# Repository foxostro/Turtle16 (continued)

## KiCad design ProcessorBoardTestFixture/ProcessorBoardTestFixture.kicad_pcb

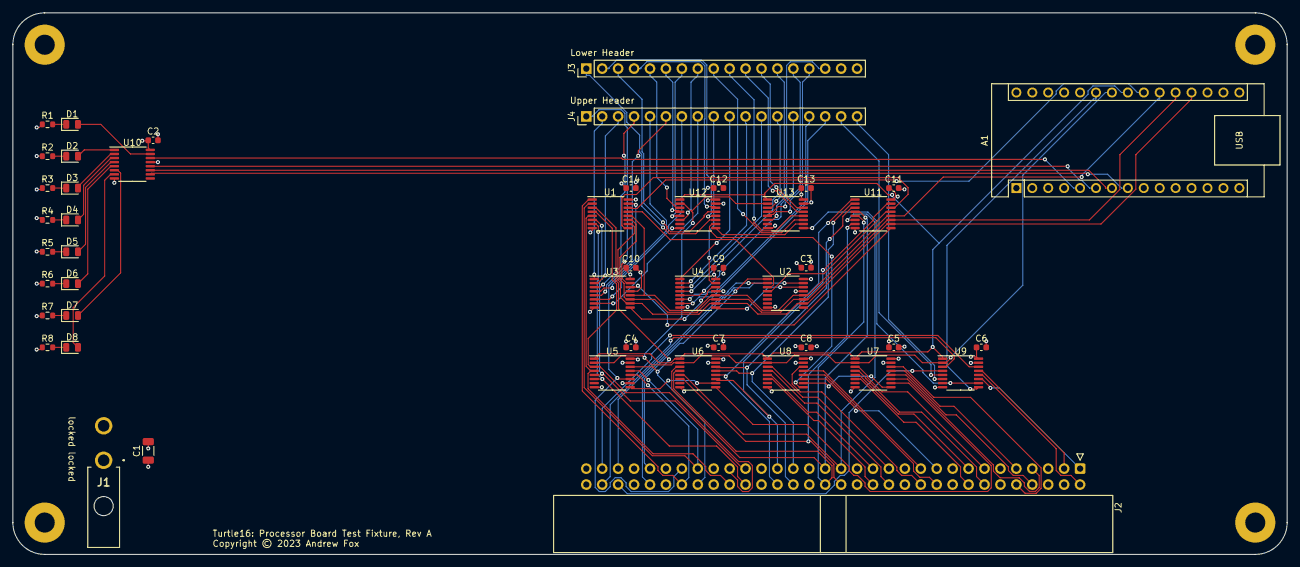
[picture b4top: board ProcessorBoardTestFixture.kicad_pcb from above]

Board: 4 copper layers, 203.2 x 86.4 mm, 52 parts (0 on the bottom side), 116 nets.

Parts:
A1: Arduino_Nano_Every; Arduino_Nano
C1: 100uF; C_1206_3216Metric
C2, C3, C4, C5, C6, C7, C8, C9, C10, C11, C12, C13, C14: 0.1uF; C_0603_1608Metric
D1, D2, D3, D4, D5, D6, D7, D8: Red; LED_0805_2012Metric
H1, H2, H3, H4: MountingHole_Pad; MountingHole_3.2mm_M3_Pad
J1: Power In; 172448-0002
J2: 71922-164LF; IDC-Header_2x32_P2.54mm_Horizontal
J3: Lower Header; PinHeader_1x18_P2.54mm_Vertical
J4: Upper Header; PinHeader_1x18_P2.54mm_Vertical
R1, R2, R3, R4, R5, R6, R7, R8: 270R; R_0603_1608Metric
U1, U2, U3, U4, U10, U11: 74HC595; TSSOP-16_4.4x5mm_P0.65mm
U5, U6, U7, U8, U9, U12, U13: 74HC165; TSSOP-16_4.4x5mm_P0.65mm

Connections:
/Instruction ROM Interface/FLUSH_IF: J4.17, U9.5 (D6)
/Instruction ROM Interface/Ins_IF0: J4.1, U3.15 (QA)
/Instruction ROM Interface/Ins_IF1: J4.2, U3.1 (QB)
/Instruction ROM Interface/Ins_IF2: J4.3, U3.2 (QC)
/Instruction ROM Interface/Ins_IF3: J4.4, U3.3 (QD)
/Instruction ROM Interface/Ins_IF4: J4.5, U3.4 (QE)
/Instruction ROM Interface/Ins_IF5: J4.6, U3.5 (QF)
/Instruction ROM Interface/Ins_IF6: J4.7, U3.6 (QG)
/Instruction ROM Interface/Ins_IF7: J4.8, U3.7 (QH)
/Instruction ROM Interface/Ins_IF8: J4.9, U4.15 (QA)
/Instruction ROM Interface/Ins_IF9: J4.10, U4.1 (QB)
/Instruction ROM Interface/Ins_IF10: J4.11, U4.2 (QC)
/Instruction ROM Interface/Ins_IF11: J4.12, U4.3 (QD)
/Instruction ROM Interface/Ins_IF12: J4.13, U4.4 (QE)
/Instruction ROM Interface/Ins_IF13: J4.14, U4.5 (QF)
/Instruction ROM Interface/Ins_IF14: J4.15, U4.6 (QG)
/Instruction ROM Interface/Ins_IF15: J4.16, U4.7 (QH)
/Instruction ROM Interface/PC0: J3.1, U12.11 (D0)
/Instruction ROM Interface/PC1: J3.2, U12.12 (D1)
/Instruction ROM Interface/PC2: J3.3, U12.13 (D2)
/Instruction ROM Interface/PC3: J3.4, U12.14 (D3)
/Instruction ROM Interface/PC4: J3.5, U12.3 (D4)
/Instruction ROM Interface/PC5: J3.6, U12.4 (D5)
/Instruction ROM Interface/PC6: J3.7, U12.5 (D6)
/Instruction ROM Interface/PC7: J3.8, U12.6 (D7)
/Instruction ROM Interface/PC8: J3.9, U13.11 (D0)
/Instruction ROM Interface/PC9: J3.10, U13.12 (D1)
/Instruction ROM Interface/PC10: J3.11, U13.13 (D2)
/Instruction ROM Interface/PC11: J3.12, U13.14 (D3)
/Instruction ROM Interface/PC12: J3.13, U13.3 (D4)
/Instruction ROM Interface/PC13: J3.14, U13.4 (D5)
/Instruction ROM Interface/PC14: J3.15, U13.5 (D6)
/Instruction ROM Interface/PC15: J3.16, U13.6 (D7)
/Instruction ROM Interface/RAMEN_R: J4.18, U9.6 (D7)
/LED Output/RCLK: A1.6 (D3), U10.12 (RCLK)
/LED Output/SCK: A1.7 (D4), U10.11 (SRCLK)
/LED Output/SI: A1.5 (D2), U10.14 (SER)
/LED Output/~CLR: A1.8 (D5), U10.10 (~SRCLR)
/System Bus Connector/Addr0: J2.7, U7.11 (D0)
/System Bus Connector/Addr1: J2.8, U7.12 (D1)
/System Bus Connector/Addr2: J2.9, U7.13 (D2)
/System Bus Connector/Addr3: J2.10, U7.14 (D3)
/System Bus Connector/Addr4: J2.13, U7.3 (D4)
/System Bus Connector/Addr5: J2.14, U7.4 (D5)
/System Bus Connector/Addr6: J2.15, U7.5 (D6)
/System Bus Connector/Addr7: J2.16, U7.6 (D7)
/System Bus Connector/Addr8: J2.19, U8.11 (D0)
/System Bus Connector/Addr9: J2.20, U8.12 (D1)
/System Bus Connector/Addr10: J2.21, U8.13 (D2)
/System Bus Connector/Addr11: J2.22, U8.14 (D3)
/System Bus Connector/Addr12: J2.25, U8.3 (D4)
/System Bus Connector/Addr13: J2.26, U8.4 (D5)
/System Bus Connector/Addr14: J2.27, U8.5 (D6)
/System Bus Connector/Addr15: J2.28, U8.6 (D7)
/System Bus Connector/Bank0: J2.1, U9.11 (D0)
/System Bus Connector/Bank1: J2.2, U9.12 (D1)
/System Bus Connector/Bank2: J2.3, U9.13 (D2)
/System Bus Connector/IO0: J2.51, U1.15 (QA), U5.11 (D0)
/System Bus Connector/IO1: J2.52, U1.1 (QB), U5.12 (D1)
/System Bus Connector/IO2: J2.49, U1.2 (QC), U5.13 (D2)
/System Bus Connector/IO3: J2.50, U1.3 (QD), U5.14 (D3)
/System Bus Connector/IO4: J2.45, U1.4 (QE), U5.3 (D4)
/System Bus Connector/IO5: J2.46, U1.5 (QF), U5.4 (D5)
/System Bus Connector/IO6: J2.43, U1.6 (QG), U5.5 (D6)
/System Bus Connector/IO7: J2.44, U1.7 (QH), U5.6 (D7)
/System Bus Connector/IO8: J2.39, U6.11 (D0), U11.15 (QA)
/System Bus Connector/IO9: J2.40, U6.12 (D1), U11.1 (QB)
/System Bus Connector/IO10: J2.37, U6.13 (D2), U11.2 (QC)
/System Bus Connector/IO11: J2.38, U6.14 (D3), U11.3 (QD)
/System Bus Connector/IO12: J2.33, U6.3 (D4), U11.4 (QE)
/System Bus Connector/IO13: J2.34, U6.4 (D5), U11.5 (QF)
/System Bus Connector/IO14: J2.31, U6.5 (D6), U11.6 (QG)
/System Bus Connector/IO15: J2.32, U6.6 (D7), U11.7 (QH)
/System Bus Connector/Phi1: J2.56, U2.15 (QA)
/System Bus Connector/Phi2: J2.55, U2.1 (QB)
/System Bus Connector/~HLT: J2.60, U9.4 (D5)
/System Bus Connector/~MemLoad: J2.62, U9.3 (D4)
/System Bus Connector/~MemStore: J2.61, U9.14 (D3)
/System Bus Connector/~RST: J2.59, U2.2 (QC)
/Test Fixture Output/OE0: U1.13 (~OE), U2.3 (QD)
/Test Fixture Output/OE1: U2.4 (QE), U11.13 (~OE)
/Test Fixture Output/RCLK: A1.21 (A2), U1.12 (RCLK), U2.12 (RCLK), U3.12 (RCLK), U4.12 (RCLK), U11.12 (RCLK)
/Test Fixture Output/SCK: A1.20 (A1), U1.11 (SRCLK), U2.11 (SRCLK), U3.11 (SRCLK), U4.11 (SRCLK), U11.11 (SRCLK)
/Test Fixture Output/SI: A1.22 (A3), U1.14 (SER)
/Test Fixture Output/~CLR: A1.19 (A0), U1.10 (~SRCLR), U2.10 (~SRCLR), U3.10 (~SRCLR), U4.10 (~SRCLR), U11.10 (~SRCLR)
/TestFixture Input/SCK: A1.24 (SCL/A5), U5.2 (CP), U6.2 (CP), U7.2 (CP), U8.2 (CP), U9.2 (CP), U12.2 (CP), U13.2 (CP)
/TestFixture Input/SO: A1.25 (A6), U9.9 (Q7)
/TestFixture Input/~PL: A1.23 (SDA/A4), U5.1 (~PL), U6.1 (~PL), U7.1 (~PL), U8.1 (~PL), U9.1 (~PL), U12.1 (~PL), U13.1 (~PL)
GND: A1.4 (GND), A1.29 (GND), C1.2, C2.2, C3.2, C4.2, C5.2, C6.2, C7.2, C8.2, C9.2, C10.2, C11.2, C12.2, C13.2, C14.2, H1.1, H2.1, H3.1, H4.1, J1.2, J2.5, J2.6, J2.11, J2.12, J2.17, J2.18, J2.23, J2.24, J2.29, J2.30, J2.35, J2.36, J2.41, J2.42, J2.47, J2.48, J2.53, J2.54, J3.17, R1.2, R2.2, R3.2, R4.2, R5.2, R6.2, R7.2, R8.2, U1.8 (GND), U2.8 (GND), U2.13 (~OE), U3.8 (GND), U3.13 (~OE), U4.8 (GND), U4.13 (~OE), U5.8 (GND), U5.10 (DS), U5.15 (~CE), U6.8 (GND), U6.15 (~CE), U7.8 (GND), U7.15 (~CE), U8.8 (GND), U8.15 (~CE), U9.8 (GND), U9.15 (~CE), U10.8 (GND), U10.13 (~OE), U11.8 (GND), U12.8 (GND), U12.15 (~CE), U13.8 (GND), U13.15 (~CE)
unnamed: D1.2 (A), U10.15 (QA)
unnamed: D1.1 (K), R1.1
unnamed: D2.2 (A), U10.1 (QB)
unnamed: D2.1 (K), R2.1
unnamed: D3.2 (A), U10.2 (QC)
unnamed: D3.1 (K), R3.1
unnamed: D4.2 (A), U10.3 (QD)
unnamed: D4.1 (K), R4.1
unnamed: D5.2 (A), U10.4 (QE)
unnamed: D5.1 (K), R5.1
unnamed: D6.2 (A), U10.5 (QF)
unnamed: D6.1 (K), R6.1
unnamed: D7.2 (A), U10.6 (QG)
unnamed: D7.1 (K), R7.1
unnamed: D8.2 (A), U10.7 (QH)
unnamed: D8.1 (K), R8.1
unnamed: U1.9 (QH'), U11.14 (SER)
unnamed: U2.14 (SER), U4.9 (QH')
unnamed: U3.9 (QH'), U4.14 (SER)
unnamed: U5.9 (Q7), U6.10 (DS)
unnamed: U6.9 (Q7), U7.10 (DS)
unnamed: U7.9 (Q7), U8.10 (DS)
unnamed: U3.14 (SER), U11.9 (QH')
unnamed: U8.9 (Q7), U12.10 (DS)
unnamed: U12.9 (Q7), U13.10 (DS)
unnamed: U9.10 (DS), U13.9 (Q7)
VCC: A1.3 (~RESET), A1.28 (~RESET), A1.30 (VIN), C1.1, C2.1, C3.1, C4.1, C5.1, C6.1, C7.1, C8.1, C9.1, C10.1, C11.1, C12.1, C13.1, C14.1, J1.1, J2.57, J2.58, J2.63, J2.64, J3.18, U1.16 (VCC), U2.16 (VCC), U3.16 (VCC), U4.16 (VCC), U5.16 (VCC), U6.16 (VCC), U7.16 (VCC), U8.16 (VCC), U9.16 (VCC), U10.16 (VCC), U11.16 (VCC), U12.16 (VCC), U13.16 (VCC)

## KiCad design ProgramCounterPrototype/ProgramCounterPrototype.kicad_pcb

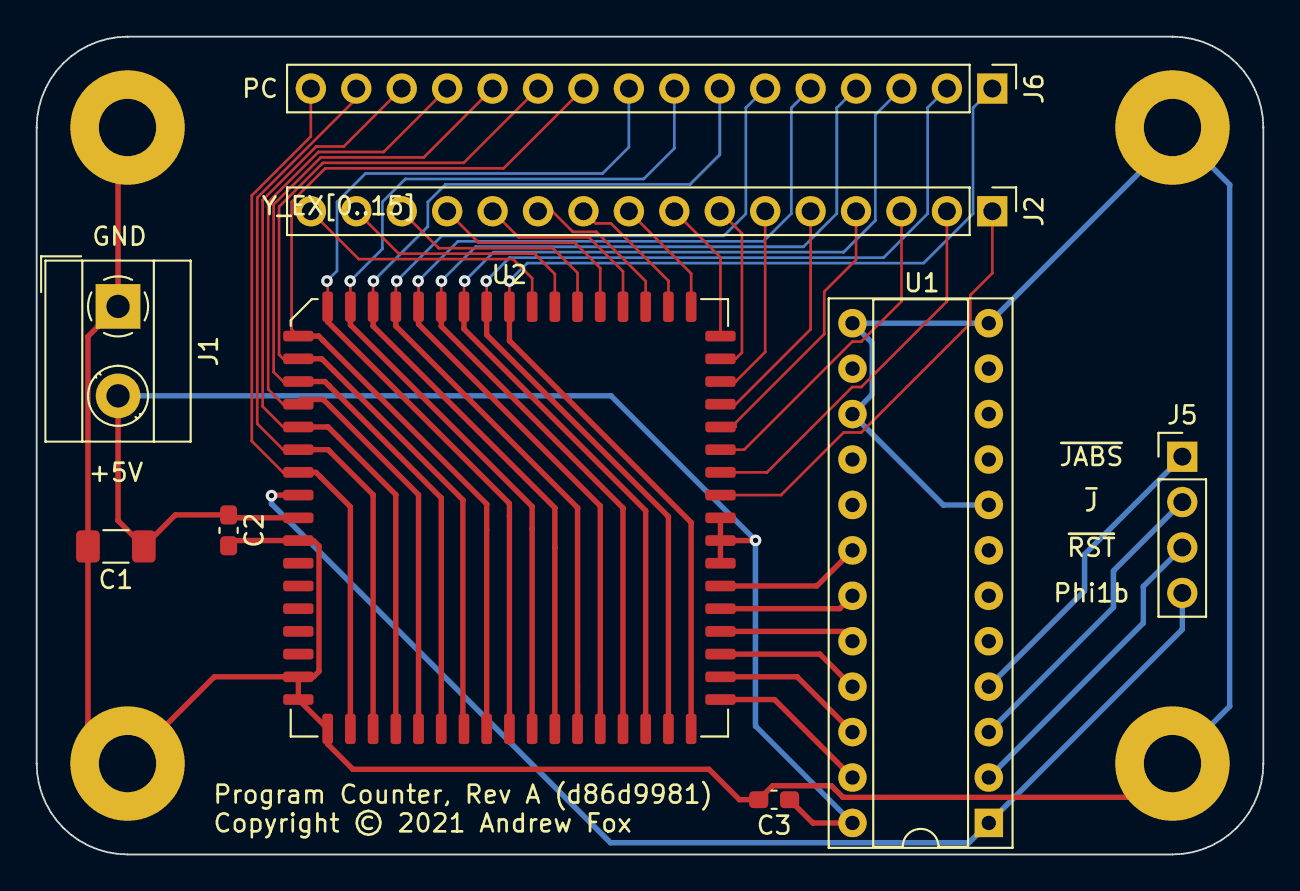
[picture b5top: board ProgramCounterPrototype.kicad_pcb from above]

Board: 2 copper layers, 68.6 x 45.7 mm, 13 parts (0 on the bottom side), 44 nets.

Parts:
C1: 100µF; C_1206_3216Metric_Pad1.33x1.80mm_HandSolder
C2, C3: 100nF; C_0603_1608Metric_Pad1.08x0.95mm_HandSolder
H1, H2, H3, H4: MountingHole_Pad; MountingHole_3.2mm_M3_Pad
J1: Screw_Terminal_01x02; TerminalBlock_MetzConnect_Type055_RT01502HDWU_1x02_P5.00mm_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
J2: Y_EX[0..15]; PinHeader_1x16_P2.54mm_Vertical
J5: Ctl; PinHeader_1x04_P2.54mm_Vertical
J6: PC; PinHeader_1x16_P2.54mm_Vertical
U1: ATF22V10C-7PX; DIP-24_W7.62mm_Socket
U2: IDT7381; PLCC-68_24.2x24.2mm_P1.27mm

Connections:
/PC0: J6.1, U2.1, U2.43
/PC1: J6.2, U2.2, U2.42
/PC2: J6.3, U2.3, U2.41
/PC3: J6.4, U2.4, U2.40
/PC4: J6.5, U2.5, U2.39
/PC5: J6.6, U2.6, U2.38
/PC6: J6.7, U2.7, U2.37
/PC7: J6.8, U2.8, U2.36
/PC8: J6.9, U2.9, U2.35
/PC9: J6.10, U2.10, U2.34
/PC10: J6.11, U2.11, U2.33
/PC11: J6.12, U2.12, U2.32
/PC12: J6.13, U2.13, U2.31
/PC13: J6.14, U2.14, U2.30
/PC14: J6.15, U2.15, U2.29
/PC15: J6.16, U2.16, U2.28
/Y_EX0: J2.1, U2.53
/Y_EX1: J2.2, U2.54
/Y_EX2: J2.3, U2.55
/Y_EX3: J2.4, U2.56
/Y_EX4: J2.5, U2.57
/Y_EX5: J2.6, U2.58
/Y_EX6: J2.7, U2.59
/Y_EX7: J2.8, U2.60
/Y_EX8: J2.9, U2.61
/Y_EX9: J2.10, U2.62
/Y_EX10: J2.11, U2.63
/Y_EX11: J2.12, U2.64
/Y_EX12: J2.13, U2.65
/Y_EX13: J2.14, U2.66
/Y_EX14: J2.15, U2.67
/Y_EX15: J2.16, U2.68
/sheet606491AF/~J: J5.2, U1.3
/sheet606491AF/~JABS: J5.1, U1.4
/sheet606491AF/~RST: J5.3, U1.2
GND: C1.2, C2.2, C3.2, H1.1, H2.1, H3.1, H4.1, J1.1, U1.8, U1.12, U1.13, U1.15, U2.19, U2.25, U2.26, U2.27
unnamed: U1.18, U2.49
unnamed: U1.19, U2.48
unnamed: U1.20, U2.47
unnamed: U1.21, U2.46
unnamed: U1.22, U2.45
unnamed: U1.23, U2.44
Phi1b: J5.4, U1.1, U2.17
VCC: C1.1, C2.1, C3.1, J1.2, U1.24, U2.18, U2.50, U2.51, U2.52

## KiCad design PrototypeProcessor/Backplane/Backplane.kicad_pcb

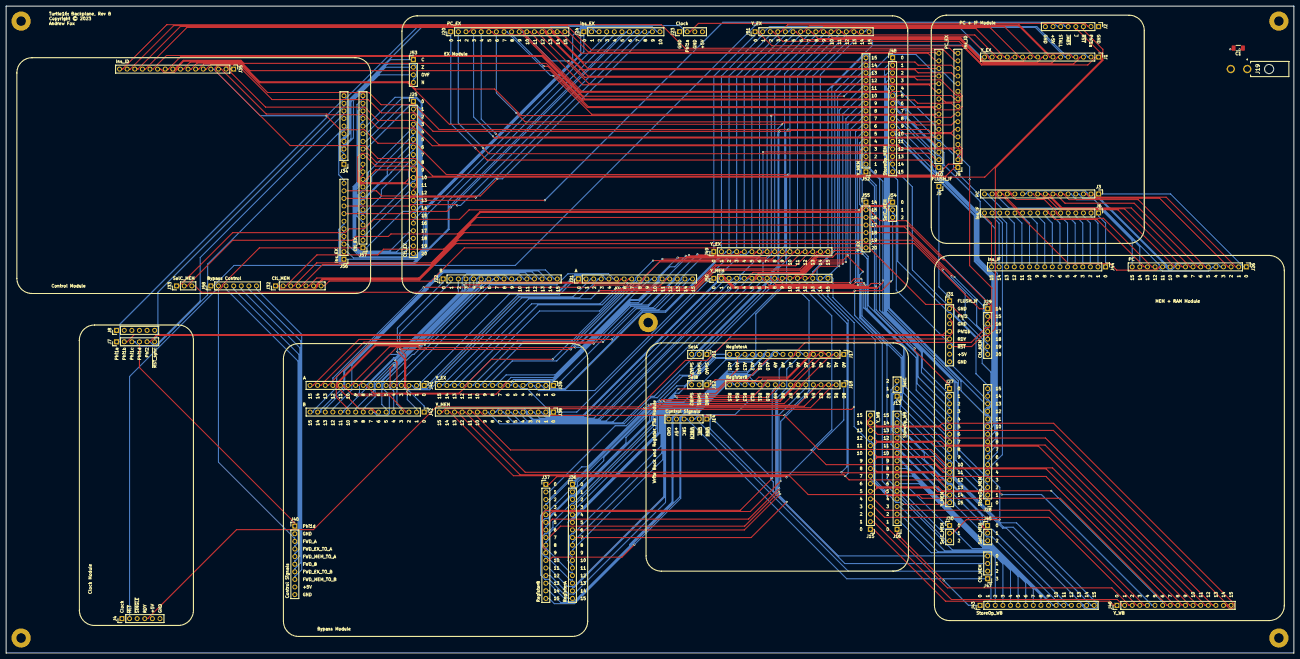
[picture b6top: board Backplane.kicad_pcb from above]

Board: 4 copper layers, 430.0 x 216.0 mm, 64 parts (0 on the bottom side), 278 nets.

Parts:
C1: 100µF; C_1206_3216Metric_Pad1.33x1.80mm_HandSolder
H1, H2, H3, H4, H5: MountingHole_Pad; MountingHole_3.2mm_M3_Pad
J1, J39, J49, J51: Y_EX; PinHeader_1x16_P2.54mm_Vertical
J2: Control Signals; PinHeader_1x08_P2.54mm_Vertical
J3, J26: PC; PinHeader_1x16_P2.54mm_Vertical
J4: Clock Inputs; PinHeader_1x06_P2.54mm_Vertical
J5: FLUSH_IF; PinHeader_1x01_P2.54mm_Vertical
J6, J44: Ins_IF; PinHeader_1x16_P2.54mm_Vertical
J7: Clock Outputs; PinHeader_1x06_P2.54mm_Vertical
J8: GND; PinHeader_1x06_P2.54mm_Vertical
J9, J35: Ins_ID; PinHeader_1x16_P2.54mm_Vertical
J10, J20: PC_EX; PinHeader_1x16_P2.54mm_Vertical
J11: SelA; PinHeader_1x03_P2.54mm_Vertical
J12: SelB; PinHeader_1x03_P2.54mm_Vertical
J13: SelC; PinHeader_1x03_P2.54mm_Vertical
J14: Control Signals; PinHeader_1x06_P2.54mm_Vertical
J15, J46: Y_WB; PinHeader_1x16_P2.54mm_Vertical
J16, J43: StoreOp_WB; PinHeader_1x16_P2.54mm_Vertical
J17, J36: RegisterA; PinHeader_1x16_P2.54mm_Vertical
J18, J37: RegisterB; PinHeader_1x16_P2.54mm_Vertical
J19: Power; 172448-0002
J21, J41: A; PinHeader_1x16_P2.54mm_Vertical
J22, J42: B; PinHeader_1x16_P2.54mm_Vertical
J23: Clock; PinHeader_1x04_P2.54mm_Vertical
J24, J56: Ins_EX; PinHeader_1x11_P2.54mm_Vertical
J25, J57: Ctl_EX; PinHeader_1x21_P2.54mm_Vertical
J27, J38, J50, J52: Y_MEM; PinHeader_1x16_P2.54mm_Vertical
J28, J48: StoreOp_MEM; PinHeader_1x16_P2.54mm_Vertical
J29, J32: Ctl_MEM; PinHeader_1x07_P2.54mm_Vertical
J30, J33, J45, J54: SelC_MEM; PinHeader_1x03_P2.54mm_Vertical
J31: Control Signals; PinHeader_1x09_P2.54mm_Vertical
J34, J40: Control Signals; PinHeader_1x10_P2.54mm_Vertical
J47: Ctl_MEM; PinHeader_1x04_P2.54mm_Vertical
J53: Flags; PinHeader_1x04_P2.54mm_Vertical
J55: Y_EX; PinHeader_1x07_P2.54mm_Vertical
J58: Bypass Control; PinHeader_1x07_P2.54mm_Vertical

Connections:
/A0: J21.1, J41.1
/A1: J21.2, J41.2
/A2: J21.3, J41.3
/A3: J21.4, J41.4
/A4: J21.5, J41.5
/A5: J21.6, J41.6
/A6: J21.7, J41.7
/A7: J21.8, J41.8
/A8: J21.9, J41.9
/A9: J21.10, J41.10
/A10: J21.11, J41.11
/A11: J21.12, J41.12
/A12: J21.13, J41.13
/A13: J21.14, J41.14
/A14: J21.15, J41.15
/A15: J21.16, J41.16
/B0: J22.1, J42.1
/B1: J22.2, J42.2
/B2: J22.3, J42.3
/B3: J22.4, J42.4
/B4: J22.5, J42.5
/B5: J22.6, J42.6
/B6: J22.7, J42.7
/B7: J22.8, J42.8
/B8: J22.9, J42.9
/B9: J22.10, J42.10
/B10: J22.11, J42.11
/B11: J22.12, J42.12
/B12: J22.13, J42.13
/B13: J22.14, J42.14
/B14: J22.15, J42.15
/B15: J22.16, J42.16
/Carry: J34.1, J53.1
/Ctl_EX0: J4.2, J25.1, J57.1
/Ctl_EX1: J25.2, J57.2
/Ctl_EX2: J25.3, J57.3
/Ctl_EX3: J25.4, J57.4
/Ctl_EX4: J25.5, J57.5
/Ctl_EX5: J25.6, J57.6
/Ctl_EX6: J25.7, J57.7
/Ctl_EX7: J25.8, J57.8
/Ctl_EX8: J25.9, J57.9
/Ctl_EX9: J25.10, J57.10
/Ctl_EX10: J25.11, J57.11
/Ctl_EX11: J25.12, J57.12
/Ctl_EX12: J2.4, J25.13, J57.13
/Ctl_EX13: J2.5, J25.14, J57.14
/Ctl_EX14: J25.15, J57.15
/Ctl_EX15: J25.16, J57.16
/Ctl_EX16: J25.17, J57.17
/Ctl_EX17: J25.18, J57.18
/Ctl_EX18: J25.19, J57.19
/Ctl_EX19: J25.20, J57.20
/Ctl_EX20: J25.21, J57.21
/Ctl_MEM14: J29.1, J32.1, J55.1
/Ctl_MEM15: J29.2, J32.2, J55.2
/Ctl_MEM16: J29.3, J32.3, J55.3
/Ctl_MEM17: J29.4, J32.4, J55.4
/Ctl_MEM18: J29.5, J32.5, J55.5
/Ctl_MEM19: J29.6, J32.6, J55.6
/Ctl_MEM20: J29.7, J32.7, J55.7
/Ctl_WB17: J14.4, J47.1
/Ctl_WB18: J14.2, J47.2
/Ctl_WB19: J14.1, J47.3
/Ctl_WB20: J14.3, J47.4
/FLUSH_IF: J5.1, J31.1
/FWD_A: J40.3, J58.2
/FWD_B: J40.6, J58.5
/FWD_EX_TO_A: J40.4, J58.3
/FWD_EX_TO_B: J40.7, J58.6
/FWD_MEM_TO_A: J40.5, J58.4
/FWD_MEM_TO_B: J40.8, J58.7
/Ins_EX0: J24.1, J56.1
/Ins_EX1: J24.2, J56.2
/Ins_EX2: J24.3, J56.3
/Ins_EX3: J24.4, J56.4
/Ins_EX4: J24.5, J56.5
/Ins_EX5: J24.6, J56.6
/Ins_EX6: J24.7, J56.7
/Ins_EX7: J24.8, J56.8
/Ins_EX8: J24.9, J56.9
/Ins_EX9: J24.10, J56.10
/Ins_EX10: J24.11, J56.11
/Ins_ID0: J9.1, J35.1
/Ins_ID1: J9.2, J35.2
/Ins_ID2: J9.3, J12.1, J35.3
/Ins_ID3: J9.4, J12.2, J35.4
/Ins_ID4: J9.5, J12.3, J35.5
/Ins_ID5: J9.6, J11.1, J35.6
/Ins_ID6: J9.7, J11.2, J35.7
/Ins_ID7: J9.8, J11.3, J35.8
/Ins_ID8: J9.9, J35.9
/Ins_ID9: J9.10, J35.10
/Ins_ID10: J9.11, J35.11
/Ins_ID11: J9.12, J35.12
/Ins_ID12: J9.13, J35.13
/Ins_ID13: J9.14, J35.14
/Ins_ID14: J9.15, J35.15
/Ins_ID15: J9.16, J35.16
/Ins_IF0: J6.1, J44.1
/Ins_IF1: J6.2, J44.2
/Ins_IF2: J6.3, J44.3
/Ins_IF3: J6.4, J44.4
/Ins_IF4: J6.5, J44.5
/Ins_IF5: J6.6, J44.6
/Ins_IF6: J6.7, J44.7
/Ins_IF7: J6.8, J44.8
/Ins_IF8: J6.9, J44.9
/Ins_IF9: J6.10, J44.10
/Ins_IF10: J6.11, J44.11
/Ins_IF11: J6.12, J44.12
/Ins_IF12: J6.13, J44.13
/Ins_IF13: J6.14, J44.14
/Ins_IF14: J6.15, J44.15
/Ins_IF15: J6.16, J44.16
/N: J34.4, J53.4
/OVF: J34.3, J53.3
/PC0: J3.1, J26.1
/PC1: J3.2, J26.2
/PC2: J3.3, J26.3
/PC3: J3.4, J26.4
/PC4: J3.5, J26.5
/PC5: J3.6, J26.6
/PC6: J3.7, J26.7
/PC7: J3.8, J26.8
/PC8: J3.9, J26.9
/PC9: J3.10, J26.10
/PC10: J3.11, J26.11
/PC11: J3.12, J26.12
/PC12: J3.13, J26.13
/PC13: J3.14, J26.14
/PC14: J3.15, J26.15
/PC15: J3.16, J26.16
/PC_EX0: J10.1, J20.1
/PC_EX1: J10.2, J20.2
/PC_EX2: J10.3, J20.3
/PC_EX3: J10.4, J20.4
/PC_EX4: J10.5, J20.5
/PC_EX5: J10.6, J20.6
/PC_EX6: J10.7, J20.7
/PC_EX7: J10.8, J20.8
/PC_EX8: J10.9, J20.9
/PC_EX9: J10.10, J20.10
/PC_EX10: J10.11, J20.11
/PC_EX11: J10.12, J20.12
/PC_EX12: J10.13, J20.13
/PC_EX13: J10.14, J20.14
/PC_EX14: J10.15, J20.15
/PC_EX15: J10.16, J20.16
/Phi1a: J2.2, J7.1, J23.2
/Phi1b: J7.2, J31.5
/Phi1c: J7.3, J34.6
/Phi1d: J7.4, J40.1
/Phi2: J7.5, J31.3, J34.8
/RDY: J4.4, J31.6
/RegisterA0: J17.1, J36.1
/RegisterA1: J17.2, J36.2
/RegisterA2: J17.3, J36.3
/RegisterA3: J17.4, J36.4
/RegisterA4: J17.5, J36.5
/RegisterA5: J17.6, J36.6
/RegisterA6: J17.7, J36.7
/RegisterA7: J17.8, J36.8
/RegisterA8: J17.9, J36.9
/RegisterA9: J17.10, J36.10
/RegisterA10: J17.11, J36.11
/RegisterA11: J17.12, J36.12
/RegisterA12: J17.13, J36.13
/RegisterA13: J17.14, J36.14
/RegisterA14: J17.15, J36.15
/RegisterA15: J17.16, J36.16
/RegisterB0: J18.1, J37.1
/RegisterB1: J18.2, J37.2
/RegisterB2: J18.3, J37.3
/RegisterB3: J18.4, J37.4
/RegisterB4: J18.5, J37.5
/RegisterB5: J18.6, J37.6
/RegisterB6: J18.7, J37.7
/RegisterB7: J18.8, J37.8
/RegisterB8: J18.9, J37.9
/RegisterB9: J18.10, J37.10
/RegisterB10: J18.11, J37.11
/RegisterB11: J18.12, J37.12
/RegisterB12: J18.13, J37.13
/RegisterB13: J18.14, J37.14
/RegisterB14: J18.15, J37.15
/RegisterB15: J18.16, J37.16
/STALL: J2.6, J58.1
/SelC_MEM0: J30.1, J33.1, J54.1
/SelC_MEM1: J30.2, J33.2, J54.2
/SelC_MEM2: J30.3, J33.3, J54.3
/SelC_WB0: J13.1, J45.1
/SelC_WB1: J13.2, J45.2
/SelC_WB2: J13.3, J45.3
/StoreOp_MEM0: J28.1, J48.1
/StoreOp_MEM1: J28.2, J48.2
/StoreOp_MEM2: J28.3, J48.3
/StoreOp_MEM3: J28.4, J48.4
/StoreOp_MEM4: J28.5, J48.5
/StoreOp_MEM5: J28.6, J48.6
/StoreOp_MEM6: J28.7, J48.7
/StoreOp_MEM7: J28.8, J48.8
/StoreOp_MEM8: J28.9, J48.9
/StoreOp_MEM9: J28.10, J48.10
/StoreOp_MEM10: J28.11, J48.11
/StoreOp_MEM11: J28.12, J48.12
/StoreOp_MEM12: J28.13, J48.13
/StoreOp_MEM13: J28.14, J48.14
/StoreOp_MEM14: J28.15, J48.15
/StoreOp_MEM15: J28.16, J48.16
/StoreOp_WB0: J16.1, J43.1
/StoreOp_WB1: J16.2, J43.2
/StoreOp_WB2: J16.3, J43.3
/StoreOp_WB3: J16.4, J43.4
/StoreOp_WB4: J16.5, J43.5
/StoreOp_WB5: J16.6, J43.6
/StoreOp_WB6: J16.7, J43.7
/StoreOp_WB7: J16.8, J43.8
/StoreOp_WB8: J16.9, J43.9
/StoreOp_WB9: J16.10, J43.10
/StoreOp_WB10: J16.11, J43.11
/StoreOp_WB11: J16.12, J43.12
/StoreOp_WB12: J16.13, J43.13
/StoreOp_WB13: J16.14, J43.14
/StoreOp_WB14: J16.15, J43.15
/StoreOp_WB15: J16.16, J43.16
/Y_EX0: J1.1, J39.1, J49.1, J51.1
/Y_EX1: J1.2, J39.2, J49.2, J51.2
/Y_EX2: J1.3, J39.3, J49.3, J51.3
/Y_EX3: J1.4, J39.4, J49.4, J51.4
/Y_EX4: J1.5, J39.5, J49.5, J51.5
/Y_EX5: J1.6, J39.6, J49.6, J51.6
/Y_EX6: J1.7, J39.7, J49.7, J51.7
/Y_EX7: J1.8, J39.8, J49.8, J51.8
/Y_EX8: J1.9, J39.9, J49.9, J51.9
/Y_EX9: J1.10, J39.10, J49.10, J51.10
/Y_EX10: J1.11, J39.11, J49.11, J51.11
/Y_EX11: J1.12, J39.12, J49.12, J51.12
/Y_EX12: J1.13, J39.13, J49.13, J51.13
/Y_EX13: J1.14, J39.14, J49.14, J51.14
/Y_EX14: J1.15, J39.15, J49.15, J51.15
/Y_EX15: J1.16, J39.16, J49.16, J51.16
/Y_MEM0: J27.1, J38.1, J50.1, J52.1
/Y_MEM1: J27.2, J38.2, J50.2, J52.2
/Y_MEM2: J27.3, J38.3, J50.3, J52.3
/Y_MEM3: J27.4, J38.4, J50.4, J52.4
/Y_MEM4: J27.5, J38.5, J50.5, J52.5
/Y_MEM5: J27.6, J38.6, J50.6, J52.6
/Y_MEM6: J27.7, J38.7, J50.7, J52.7
/Y_MEM7: J27.8, J38.8, J50.8, J52.8
/Y_MEM8: J27.9, J38.9, J50.9, J52.9
/Y_MEM9: J27.10, J38.10, J50.10, J52.10
/Y_MEM10: J27.11, J38.11, J50.11, J52.11
/Y_MEM11: J27.12, J38.12, J50.12, J52.12
/Y_MEM12: J27.13, J38.13, J50.13, J52.13
/Y_MEM13: J27.14, J38.14, J50.14, J52.14
/Y_MEM14: J27.15, J38.15, J50.15, J52.15
/Y_MEM15: J27.16, J38.16, J50.16, J52.16
/Y_WB0: J15.1, J46.1
/Y_WB1: J15.2, J46.2
/Y_WB2: J15.3, J46.3
/Y_WB3: J15.4, J46.4
/Y_WB4: J15.5, J46.5
/Y_WB5: J15.6, J46.6
/Y_WB6: J15.7, J46.7
/Y_WB7: J15.8, J46.8
/Y_WB8: J15.9, J46.9
/Y_WB9: J15.10, J46.10
/Y_WB10: J15.11, J46.11
/Y_WB11: J15.12, J46.12
/Y_WB12: J15.13, J46.13
/Y_WB13: J15.14, J46.14
/Y_WB14: J15.15, J46.15
/Y_WB15: J15.16, J46.16
/Z: J34.2, J53.2
/~RST_sync: J2.3, J7.6, J31.7, J34.9
GND: C1.2, H1.1, H2.1, H3.1, H4.1, H5.1, J2.1, J2.8, J4.6, J8.1, J8.2, J8.3, J8.4, J8.5, J8.6, J14.6, J19.2, J23.1, J23.3, J31.2, J31.4, J31.9, J34.5, J34.7, J40.2, J40.10
VCC: C1.1, J2.7, J4.5, J14.5, J19.1, J23.4, J31.8, J34.10, J40.9

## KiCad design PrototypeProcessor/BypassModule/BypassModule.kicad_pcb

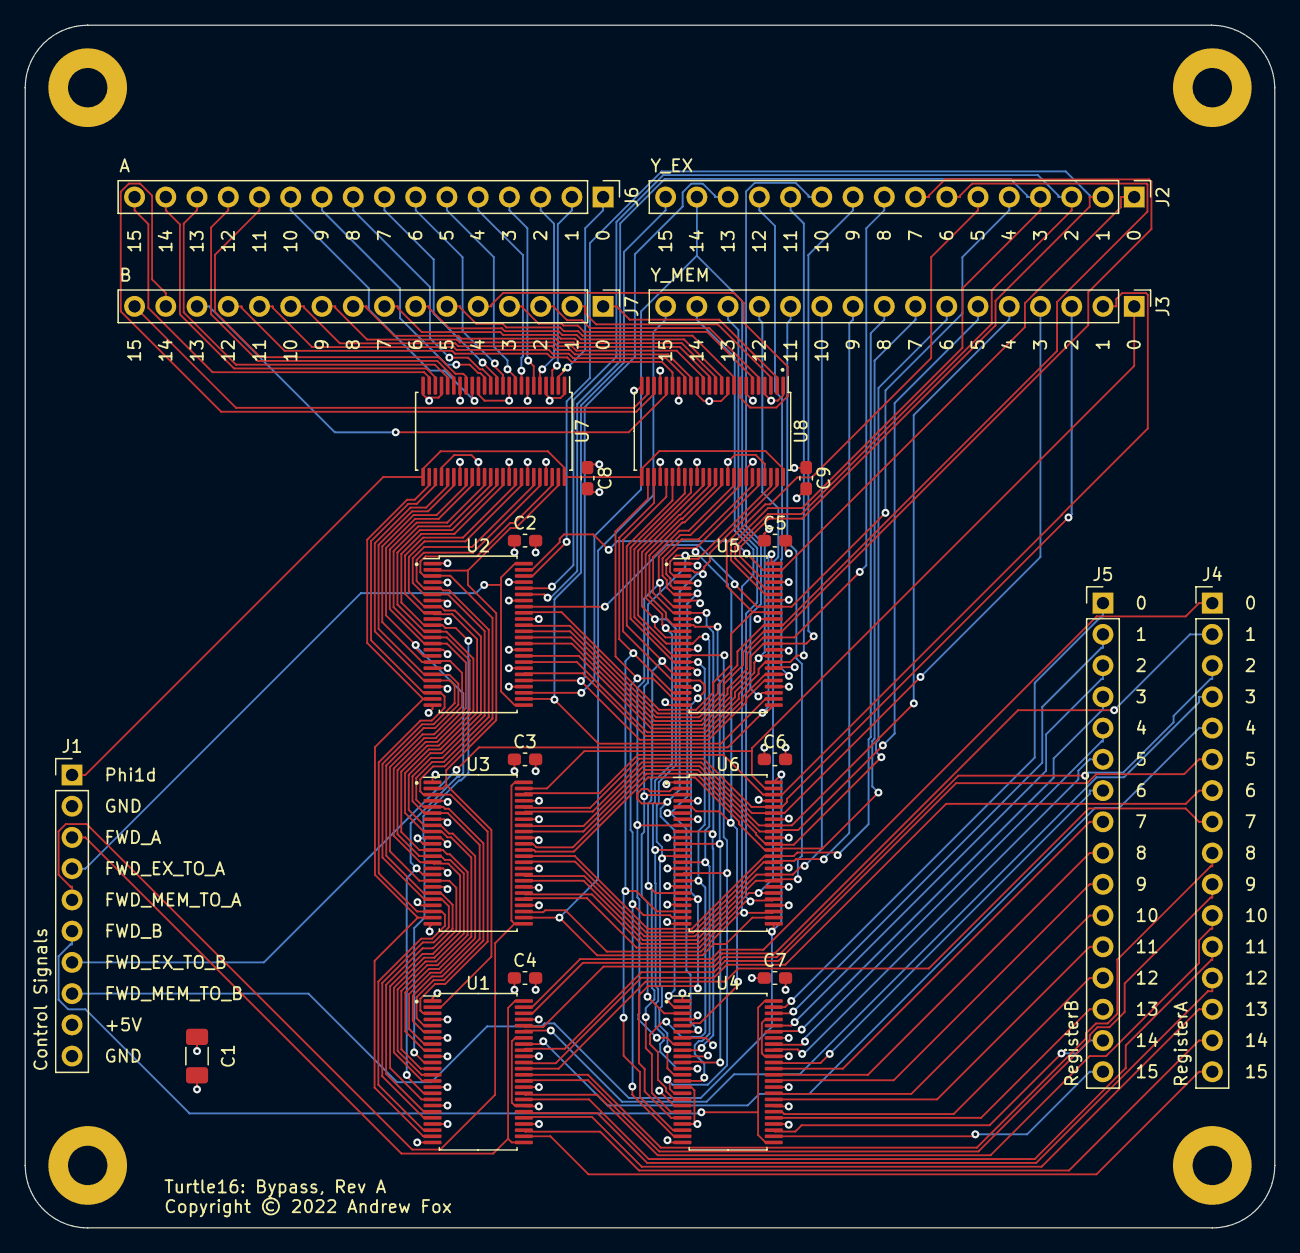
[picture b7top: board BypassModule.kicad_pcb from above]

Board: 4 copper layers, 101.6 x 97.8 mm, 28 parts (0 on the bottom side), 137 nets.

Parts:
C1: 100µF; C_1206_3216Metric_Pad1.33x1.80mm_HandSolder
C2, C3, C4, C5, C6, C7, C8, C9: 100nF; C_0603_1608Metric_Pad1.08x0.95mm_HandSolder
H1, H2, H3, H4: MountingHole_Pad; MountingHole_3.2mm_M3_Pad
J1: Control Signals; PinHeader_1x10_P2.54mm_Vertical
J2: Y_EX; PinHeader_1x16_P2.54mm_Vertical
J3: Y_MEM; PinHeader_1x16_P2.54mm_Vertical
J4: RegisterA; PinHeader_1x16_P2.54mm_Vertical
J5: RegisterB; PinHeader_1x16_P2.54mm_Vertical
J6: A; PinHeader_1x16_P2.54mm_Vertical
J7: B; PinHeader_1x16_P2.54mm_Vertical
U1, U2, U3, U4, U5, U6: 74AHCT16245; TSSOP-48_6.1x12.5mm_P0.5mm
U7, U8: 74ABT16374; TSSOP-48_6.1x12.5mm_P0.5mm

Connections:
/Bypass Prototype Inputs/FWD_A: J1.3, U1.25 (2~OE), U1.48 (1~OE)
/Bypass Prototype Inputs/FWD_B: J1.6, U4.25 (2~OE), U4.48 (1~OE)
/Bypass Prototype Inputs/FWD_EX_TO_A: J1.4, U2.25 (2~OE), U2.48 (1~OE)
/Bypass Prototype Inputs/FWD_EX_TO_B: J1.7, U5.25 (2~OE), U5.48 (1~OE)
/Bypass Prototype Inputs/FWD_MEM_TO_A: J1.5, U3.25 (2~OE), U3.48 (1~OE)
/Bypass Prototype Inputs/FWD_MEM_TO_B: J1.8, U6.25 (2~OE), U6.48 (1~OE)
/Bypass Prototype Inputs/Phi1d: J1.1, U7.25 (2CLK), U7.48 (1CLK), U8.25 (2CLK), U8.48 (1CLK)
/Bypass Prototype Inputs/RegisterA0: J4.1, U1.47 (1A1)
/Bypass Prototype Inputs/RegisterA1: J4.2, U1.46 (1A2)
/Bypass Prototype Inputs/RegisterA2: J4.3, U1.44 (1A3)
/Bypass Prototype Inputs/RegisterA3: J4.4, U1.43 (1A4)
/Bypass Prototype Inputs/RegisterA4: J4.5, U1.41 (1A5)
/Bypass Prototype Inputs/RegisterA5: J4.6, U1.40 (1A6)
/Bypass Prototype Inputs/RegisterA6: J4.7, U1.38 (1A7)
/Bypass Prototype Inputs/RegisterA7: J4.8, U1.37 (1A8)
/Bypass Prototype Inputs/RegisterA8: J4.9, U1.36 (2A1)
/Bypass Prototype Inputs/RegisterA9: J4.10, U1.35 (2A2)
/Bypass Prototype Inputs/RegisterA10: J4.11, U1.33 (2A3)
/Bypass Prototype Inputs/RegisterA11: J4.12, U1.32 (2A4)
/Bypass Prototype Inputs/RegisterA12: J4.13, U1.30 (2A5)
/Bypass Prototype Inputs/RegisterA13: J4.14, U1.29 (2A6)
/Bypass Prototype Inputs/RegisterA14: J4.15, U1.27 (2A7)
/Bypass Prototype Inputs/RegisterA15: J4.16, U1.26 (2A8)
/Bypass Prototype Inputs/RegisterB0: J5.1, U4.47 (1A1)
/Bypass Prototype Inputs/RegisterB1: J5.2, U4.46 (1A2)
/Bypass Prototype Inputs/RegisterB2: J5.3, U4.44 (1A3)
/Bypass Prototype Inputs/RegisterB3: J5.4, U4.43 (1A4)
/Bypass Prototype Inputs/RegisterB4: J5.5, U4.41 (1A5)
/Bypass Prototype Inputs/RegisterB5: J5.6, U4.40 (1A6)
/Bypass Prototype Inputs/RegisterB6: J5.7, U4.38 (1A7)
/Bypass Prototype Inputs/RegisterB7: J5.8, U4.37 (1A8)
/Bypass Prototype Inputs/RegisterB8: J5.9, U4.36 (2A1)
/Bypass Prototype Inputs/RegisterB9: J5.10, U4.35 (2A2)
/Bypass Prototype Inputs/RegisterB10: J5.11, U4.33 (2A3)
/Bypass Prototype Inputs/RegisterB11: J5.12, U4.32 (2A4)
/Bypass Prototype Inputs/RegisterB12: J5.13, U4.30 (2A5)
/Bypass Prototype Inputs/RegisterB13: J5.14, U4.29 (2A6)
/Bypass Prototype Inputs/RegisterB14: J5.15, U4.27 (2A7)
/Bypass Prototype Inputs/RegisterB15: J5.16, U4.26 (2A8)
/Bypass Prototype Inputs/Y_EX0: J2.1, U2.47 (1A1), U5.47 (1A1)
/Bypass Prototype Inputs/Y_EX1: J2.2, U2.46 (1A2), U5.46 (1A2)
/Bypass Prototype Inputs/Y_EX2: J2.3, U2.44 (1A3), U5.44 (1A3)
/Bypass Prototype Inputs/Y_EX3: J2.4, U2.43 (1A4), U5.43 (1A4)
/Bypass Prototype Inputs/Y_EX4: J2.5, U2.41 (1A5), U5.41 (1A5)
/Bypass Prototype Inputs/Y_EX5: J2.6, U2.40 (1A6), U5.40 (1A6)
/Bypass Prototype Inputs/Y_EX6: J2.7, U2.38 (1A7), U5.38 (1A7)
/Bypass Prototype Inputs/Y_EX7: J2.8, U2.37 (1A8), U5.37 (1A8)
/Bypass Prototype Inputs/Y_EX8: J2.9, U2.36 (2A1), U5.36 (2A1)
/Bypass Prototype Inputs/Y_EX9: J2.10, U2.35 (2A2), U5.35 (2A2)
/Bypass Prototype Inputs/Y_EX10: J2.11, U2.33 (2A3), U5.33 (2A3)
/Bypass Prototype Inputs/Y_EX11: J2.12, U2.32 (2A4), U5.32 (2A4)
/Bypass Prototype Inputs/Y_EX12: J2.13, U2.30 (2A5), U5.30 (2A5)
/Bypass Prototype Inputs/Y_EX13: J2.14, U2.29 (2A6), U5.29 (2A6)
/Bypass Prototype Inputs/Y_EX14: J2.15, U2.27 (2A7), U5.27 (2A7)
/Bypass Prototype Inputs/Y_EX15: J2.16, U2.26 (2A8), U5.26 (2A8)
/Bypass Prototype Inputs/Y_MEM0: J3.1, U3.47 (1A1), U6.47 (1A1)
/Bypass Prototype Inputs/Y_MEM1: J3.2, U3.46 (1A2), U6.46 (1A2)
/Bypass Prototype Inputs/Y_MEM2: J3.3, U3.44 (1A3), U6.44 (1A3)
/Bypass Prototype Inputs/Y_MEM3: J3.4, U3.43 (1A4), U6.43 (1A4)
/Bypass Prototype Inputs/Y_MEM4: J3.5, U3.41 (1A5), U6.41 (1A5)
/Bypass Prototype Inputs/Y_MEM5: J3.6, U3.40 (1A6), U6.40 (1A6)
/Bypass Prototype Inputs/Y_MEM6: J3.7, U3.38 (1A7), U6.38 (1A7)
/Bypass Prototype Inputs/Y_MEM7: J3.8, U3.37 (1A8), U6.37 (1A8)
/Bypass Prototype Inputs/Y_MEM8: J3.9, U3.36 (2A1), U6.36 (2A1)
/Bypass Prototype Inputs/Y_MEM9: J3.10, U3.35 (2A2), U6.35 (2A2)
/Bypass Prototype Inputs/Y_MEM10: J3.11, U3.33 (2A3), U6.33 (2A3)
/Bypass Prototype Inputs/Y_MEM11: J3.12, U3.32 (2A4), U6.32 (2A4)
/Bypass Prototype Inputs/Y_MEM12: J3.13, U3.30 (2A5), U6.30 (2A5)
/Bypass Prototype Inputs/Y_MEM13: J3.14, U3.29 (2A6), U6.29 (2A6)
/Bypass Prototype Inputs/Y_MEM14: J3.15, U3.27 (2A7), U6.27 (2A7)
/Bypass Prototype Inputs/Y_MEM15: J3.16, U3.26 (2A8), U6.26 (2A8)
/BypassPrototypeOutputs/A0: J6.1, U7.2 (1Q1)
/BypassPrototypeOutputs/A1: J6.2, U7.3 (1Q2)
/BypassPrototypeOutputs/A2: J6.3, U7.5 (1Q3)
/BypassPrototypeOutputs/A3: J6.4, U7.6 (1Q4)
/BypassPrototypeOutputs/A4: J6.5, U7.8 (1Q5)
/BypassPrototypeOutputs/A5: J6.6, U7.9 (1Q6)
/BypassPrototypeOutputs/A6: J6.7, U7.11 (1Q7)
/BypassPrototypeOutputs/A7: J6.8, U7.12 (1Q8)
/BypassPrototypeOutputs/A8: J6.9, U7.13 (2Q1)
/BypassPrototypeOutputs/A9: J6.10, U7.14 (2Q2)
/BypassPrototypeOutputs/A10: J6.11, U7.16 (2Q3)
/BypassPrototypeOutputs/A11: J6.12, U7.17 (2Q4)
/BypassPrototypeOutputs/A12: J6.13, U7.19 (2Q5)
/BypassPrototypeOutputs/A13: J6.14, U7.20 (2Q6)
/BypassPrototypeOutputs/A14: J6.15, U7.22 (2Q7)
/BypassPrototypeOutputs/A15: J6.16, U7.23 (2Q8)
/BypassPrototypeOutputs/B0: J7.1, U8.2 (1Q1)
/BypassPrototypeOutputs/B1: J7.2, U8.3 (1Q2)
/BypassPrototypeOutputs/B2: J7.3, U8.5 (1Q3)
/BypassPrototypeOutputs/B3: J7.4, U8.6 (1Q4)
/BypassPrototypeOutputs/B4: J7.5, U8.8 (1Q5)
/BypassPrototypeOutputs/B5: J7.6, U8.9 (1Q6)
/BypassPrototypeOutputs/B6: J7.7, U8.11 (1Q7)
/BypassPrototypeOutputs/B7: J7.8, U8.12 (1Q8)
/BypassPrototypeOutputs/B8: J7.9, U8.13 (2Q1)
/BypassPrototypeOutputs/B9: J7.10, U8.14 (2Q2)
/BypassPrototypeOutputs/B10: J7.11, U8.16 (2Q3)
/BypassPrototypeOutputs/B11: J7.12, U8.17 (2Q4)
/BypassPrototypeOutputs/B12: J7.13, U8.19 (2Q5)
/BypassPrototypeOutputs/B13: J7.14, U8.20 (2Q6)
/BypassPrototypeOutputs/B14: J7.15, U8.22 (2Q7)
/BypassPrototypeOutputs/B15: J7.16, U8.23 (2Q8)
/Operand Forwarding A/A_ID0: U1.2 (1B1), U2.2 (1B1), U3.2 (1B1), U7.47 (1D1)
/Operand Forwarding A/A_ID1: U1.3 (1B2), U2.3 (1B2), U3.3 (1B2), U7.46 (1D2)
/Operand Forwarding A/A_ID2: U1.5 (1B3), U2.5 (1B3), U3.5 (1B3), U7.44 (1D3)
/Operand Forwarding A/A_ID3: U1.6 (1B4), U2.6 (1B4), U3.6 (1B4), U7.43 (1D4)
/Operand Forwarding A/A_ID4: U1.8 (1B5), U2.8 (1B5), U3.8 (1B5), U7.41 (1D5)
/Operand Forwarding A/A_ID5: U1.9 (1B6), U2.9 (1B6), U3.9 (1B6), U7.40 (1D6)
/Operand Forwarding A/A_ID6: U1.11 (1B7), U2.11 (1B7), U3.11 (1B7), U7.38 (1D7)
/Operand Forwarding A/A_ID7: U1.12 (1B8), U2.12 (1B8), U3.12 (1B8), U7.37 (1D8)
/Operand Forwarding A/A_ID8: U1.13 (2B1), U2.13 (2B1), U3.13 (2B1), U7.36 (2D1)
/Operand Forwarding A/A_ID9: U1.14 (2B2), U2.14 (2B2), U3.14 (2B2), U7.35 (2D2)
/Operand Forwarding A/A_ID10: U1.16 (2B3), U2.16 (2B3), U3.16 (2B3), U7.33 (2D3)
/Operand Forwarding A/A_ID11: U1.17 (2B4), U2.17 (2B4), U3.17 (2B4), U7.32 (2D4)
/Operand Forwarding A/A_ID12: U1.19 (2B5), U2.19 (2B5), U3.19 (2B5), U7.30 (2D5)
/Operand Forwarding A/A_ID13: U1.20 (2B6), U2.20 (2B6), U3.20 (2B6), U7.29 (2D6)
/Operand Forwarding A/A_ID14: U1.22 (2B7), U2.22 (2B7), U3.22 (2B7), U7.27 (2D7)
/Operand Forwarding A/A_ID15: U1.23 (2B8), U2.23 (2B8), U3.23 (2B8), U7.26 (2D8)
/Operand Forwarding B/B_ID0: U4.2 (1B1), U5.2 (1B1), U6.2 (1B1), U8.47 (1D1)
/Operand Forwarding B/B_ID1: U4.3 (1B2), U5.3 (1B2), U6.3 (1B2), U8.46 (1D2)
/Operand Forwarding B/B_ID2: U4.5 (1B3), U5.5 (1B3), U6.5 (1B3), U8.44 (1D3)
/Operand Forwarding B/B_ID3: U4.6 (1B4), U5.6 (1B4), U6.6 (1B4), U8.43 (1D4)
/Operand Forwarding B/B_ID4: U4.8 (1B5), U5.8 (1B5), U6.8 (1B5), U8.41 (1D5)
/Operand Forwarding B/B_ID5: U4.9 (1B6), U5.9 (1B6), U6.9 (1B6), U8.40 (1D6)
/Operand Forwarding B/B_ID6: U4.11 (1B7), U5.11 (1B7), U6.11 (1B7), U8.38 (1D7)
/Operand Forwarding B/B_ID7: U4.12 (1B8), U5.12 (1B8), U6.12 (1B8), U8.37 (1D8)
/Operand Forwarding B/B_ID8: U4.13 (2B1), U5.13 (2B1), U6.13 (2B1), U8.36 (2D1)
/Operand Forwarding B/B_ID9: U4.14 (2B2), U5.14 (2B2), U6.14 (2B2), U8.35 (2D2)
/Operand Forwarding B/B_ID10: U4.16 (2B3), U5.16 (2B3), U6.16 (2B3), U8.33 (2D3)
/Operand Forwarding B/B_ID11: U4.17 (2B4), U5.17 (2B4), U6.17 (2B4), U8.32 (2D4)
/Operand Forwarding B/B_ID12: U4.19 (2B5), U5.19 (2B5), U6.19 (2B5), U8.30 (2D5)
/Operand Forwarding B/B_ID13: U4.20 (2B6), U5.20 (2B6), U6.20 (2B6), U8.29 (2D6)
/Operand Forwarding B/B_ID14: U4.22 (2B7), U5.22 (2B7), U6.22 (2B7), U8.27 (2D7)
/Operand Forwarding B/B_ID15: U4.23 (2B8), U5.23 (2B8), U6.23 (2B8), U8.26 (2D8)
GND: C1.2, C2.2, C3.2, C4.2, C5.2, C6.2, C7.2, C8.2, C9.2, H1.1, H2.1, H3.1, H4.1, J1.2, J1.10, U1.4 (GND), U1.10 (GND), U1.15 (GND), U1.21 (GND), U1.28 (GND), U1.34 (GND), U1.39 (GND), U1.45 (GND), U2.4 (GND), U2.10 (GND), U2.15 (GND), U2.21 (GND), U2.28 (GND), U2.34 (GND), U2.39 (GND), U2.45 (GND), U3.4 (GND), U3.10 (GND), U3.15 (GND), U3.21 (GND), U3.28 (GND), U3.34 (GND), U3.39 (GND), U3.45 (GND), U4.4 (GND), U4.10 (GND), U4.15 (GND), U4.21 (GND), U4.28 (GND), U4.34 (GND), U4.39 (GND), U4.45 (GND), U5.4 (GND), U5.10 (GND), U5.15 (GND), U5.21 (GND), U5.28 (GND), U5.34 (GND), U5.39 (GND), U5.45 (GND), U6.4 (GND), U6.10 (GND), U6.15 (GND), U6.21 (GND), U6.28 (GND), U6.34 (GND), U6.39 (GND), U6.45 (GND), U7.1 (1~OE), U7.4 (GND), U7.10 (GND), U7.15 (GND), U7.21 (GND), U7.24 (2~OE), U7.28 (GND), U7.34 (GND), U7.39 (GND), U7.45 (GND), U8.1 (1~OE), U8.4 (GND), U8.10 (GND), U8.15 (GND), U8.21 (GND), U8.24 (2~OE), U8.28 (GND), U8.34 (GND), U8.39 (GND), U8.45 (GND)
VCC: C1.1, C2.1, C3.1, C4.1, C5.1, C6.1, C7.1, C8.1, C9.1, J1.9, U1.1 (1DIR), U1.7 (VCC), U1.18 (VCC), U1.24 (2DIR), U1.31 (VCC), U1.42 (VCC), U2.1 (1DIR), U2.7 (VCC), U2.18 (VCC), U2.24 (2DIR), U2.31 (VCC), U2.42 (VCC), U3.1 (1DIR), U3.7 (VCC), U3.18 (VCC), U3.24 (2DIR), U3.31 (VCC), U3.42 (VCC), U4.1 (1DIR), U4.7 (VCC), U4.18 (VCC), U4.24 (2DIR), U4.31 (VCC), U4.42 (VCC), U5.1 (1DIR), U5.7 (VCC), U5.18 (VCC), U5.24 (2DIR), U5.31 (VCC), U5.42 (VCC), U6.1 (1DIR), U6.7 (VCC), U6.18 (VCC), U6.24 (2DIR), U6.31 (VCC), U6.42 (VCC), U7.7 (VCC), U7.18 (VCC), U7.31 (VCC), U7.42 (VCC), U8.7 (VCC), U8.18 (VCC), U8.31 (VCC), U8.42 (VCC)
